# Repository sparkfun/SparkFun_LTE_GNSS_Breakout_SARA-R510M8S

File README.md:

# SparkFun LTE GNSS Breakout - SARA-R510M8S

The u-blox SARA-R510M8S module is a secure cloud LTE Cat M1, LTE Cat NB2 solution based on u-blox's UBX-R5 cellular chipset.
The SARA-R510M8S has an integrated u-blox M8 GNSS receiver chip and a separate GNSS antenna interface.

The SARA-R5's UART interface can be configured into one of five variants, providing connectivity over one or two UARTs. A separate USB port
provides access to the SARA's trace log for diagnostic purposes. This breakout provides access to all three interfaces (UART1, UART2 and SARA Diag)
via three separate USB-C connections. All eight 3.3V serial signals are available on a 0.1"-pitch breakout header.

## Repository Contents

- **/Documentation** - Datasheets etc.
- **/Hardware** - Eagle PCB, SCH and LBR design files. Full schematic in PDF format.
- **[LICENSE.md](./LICENSE.md)** - License details

## Documentation

- **[SparkFun u-blox SARA-R5 Arduino Library](https://github.com/sparkfun/SparkFun_u-blox_SARA-R5_Arduino_Library)** - Arduino library for the SARA-R5 module.
- **[Hookup Guide](https://learn.sparkfun.com/tutorials/lte-gnss-breakout---sara-r5-hookup-guide)** - Hookup Guide for the LTE GNSS Breakout - SARA-R5.

## UART 1 & 2

The board comes pre-configured to support interface variants 0 and 1 (single UART, 8-wire connectivity). If you want to use variants 2-4 (dual UART),
you will need to:
- Open the split pads adjacent to the **DTR**, **DCD**, **RI** and **DSR** breakout pins
- Close the solder split pads labelled **TXD2**, **RXD2**, **RTS2** and **CTS2**
- Open the **OUT** split pad labelled **DSR O RTS2 I** and close the adjacent **IN** solder split pad

The serial signals on the breakout pins are all 3.3V. Level-shifting circuits connect them to the SARA's 1.8V UART pins.

## Power Options

The board can draw 5V power from any or all of the USB-C connectors. Optionally, you can provide power via the **V EXT** breakout pin: 3.7V Min; 6.0V Max.

If you want to use **V EXT** as an output, you can bypass the DVEXT protection diode by closing the **V EXT Diode** solder split pad.

The board's 3.3V current draw can be monitored via the **MEAS** header pins. Open the split pad linking these pins if required.

## Additional Breakout Pins

- **NI** - Network Indicator will be _low_ when the SARA is on and the network is available.
- **TP** - GNSS Timing Pulse (PPS) pin will pulse low/high when configured by the **+UTIME=1,1** command. Please see the [AT Commands Manual](./Documents/SARA-R5_ATCommands_(UBX-19047455).pdf) for more details.
- **SARA On** - pull low for 5 seconds then release to turn the SARA off. Pull low briefly again to turn the SARA back on. You can tell if the SARA is powered by monitoring the **VCCIO** 1.8V pin.
- **INT** - by default this pin is connected to the SARA's bi-directional **EXT INT** pin. It can optionally be connected to **GPIO3** by reconfiguring the **SARA INT** split pad.
- **~RESET** - pull low and release to reset the SARA.
- **SARA I<sup>2</sup>C** - provides access to the SARA's I<sup>2</sup>C SDA and SCL pins.
- **3V3EN** - pull this pin low to disable the 3.3V supply completely. _Note: you may want to turn the SARA off using the **SARA On** pin first, so it disconnects from the network correctly._

**NI**, **TP**, **SARA On**, **INT**, **~RESET**, **SDA** and **SCL** are all 3.3V. Level-shifting circuits connect them to the SARA's 1.8V I/O pins.

_**Important Note**: **VCCIO** is 1.8V. You may need to connect it to an analog input to sense the voltage correctly._

_**Important Note**: **3V3EN** is pulled-up to VIN (5V) via a 100K resistor. We recommend using a switch or open-collector / open-drain output to pull **3V3EN** low._

## Switches

- **Reset** - pressing this switch will reset the SARA.
- **SARA On** - pressing and holding this switch for five seconds will turn the SARA off. Press briefly to turn the SARA back on again.

## GNSS Antenna Power

The board provides 3.3V power for an active GNSS antenna. By default the antenna power is enabled whenever the SARA is on. You can reconfigure the **ANT GNSS PWR**
split pad to optionally control the antenna power via the SARA's GPIO2 pin.

The GPIO2 pin can be controlled using the **+UGPIOC=23,0,1** command.
Please see the [AT Commands Manual](./Documents/SARA-R5_ATCommands_(UBX-19047455).pdf) for more details.

## Product Versions

- [GPS-18031](https://www.sparkfun.com/products/18031) - Initial Release

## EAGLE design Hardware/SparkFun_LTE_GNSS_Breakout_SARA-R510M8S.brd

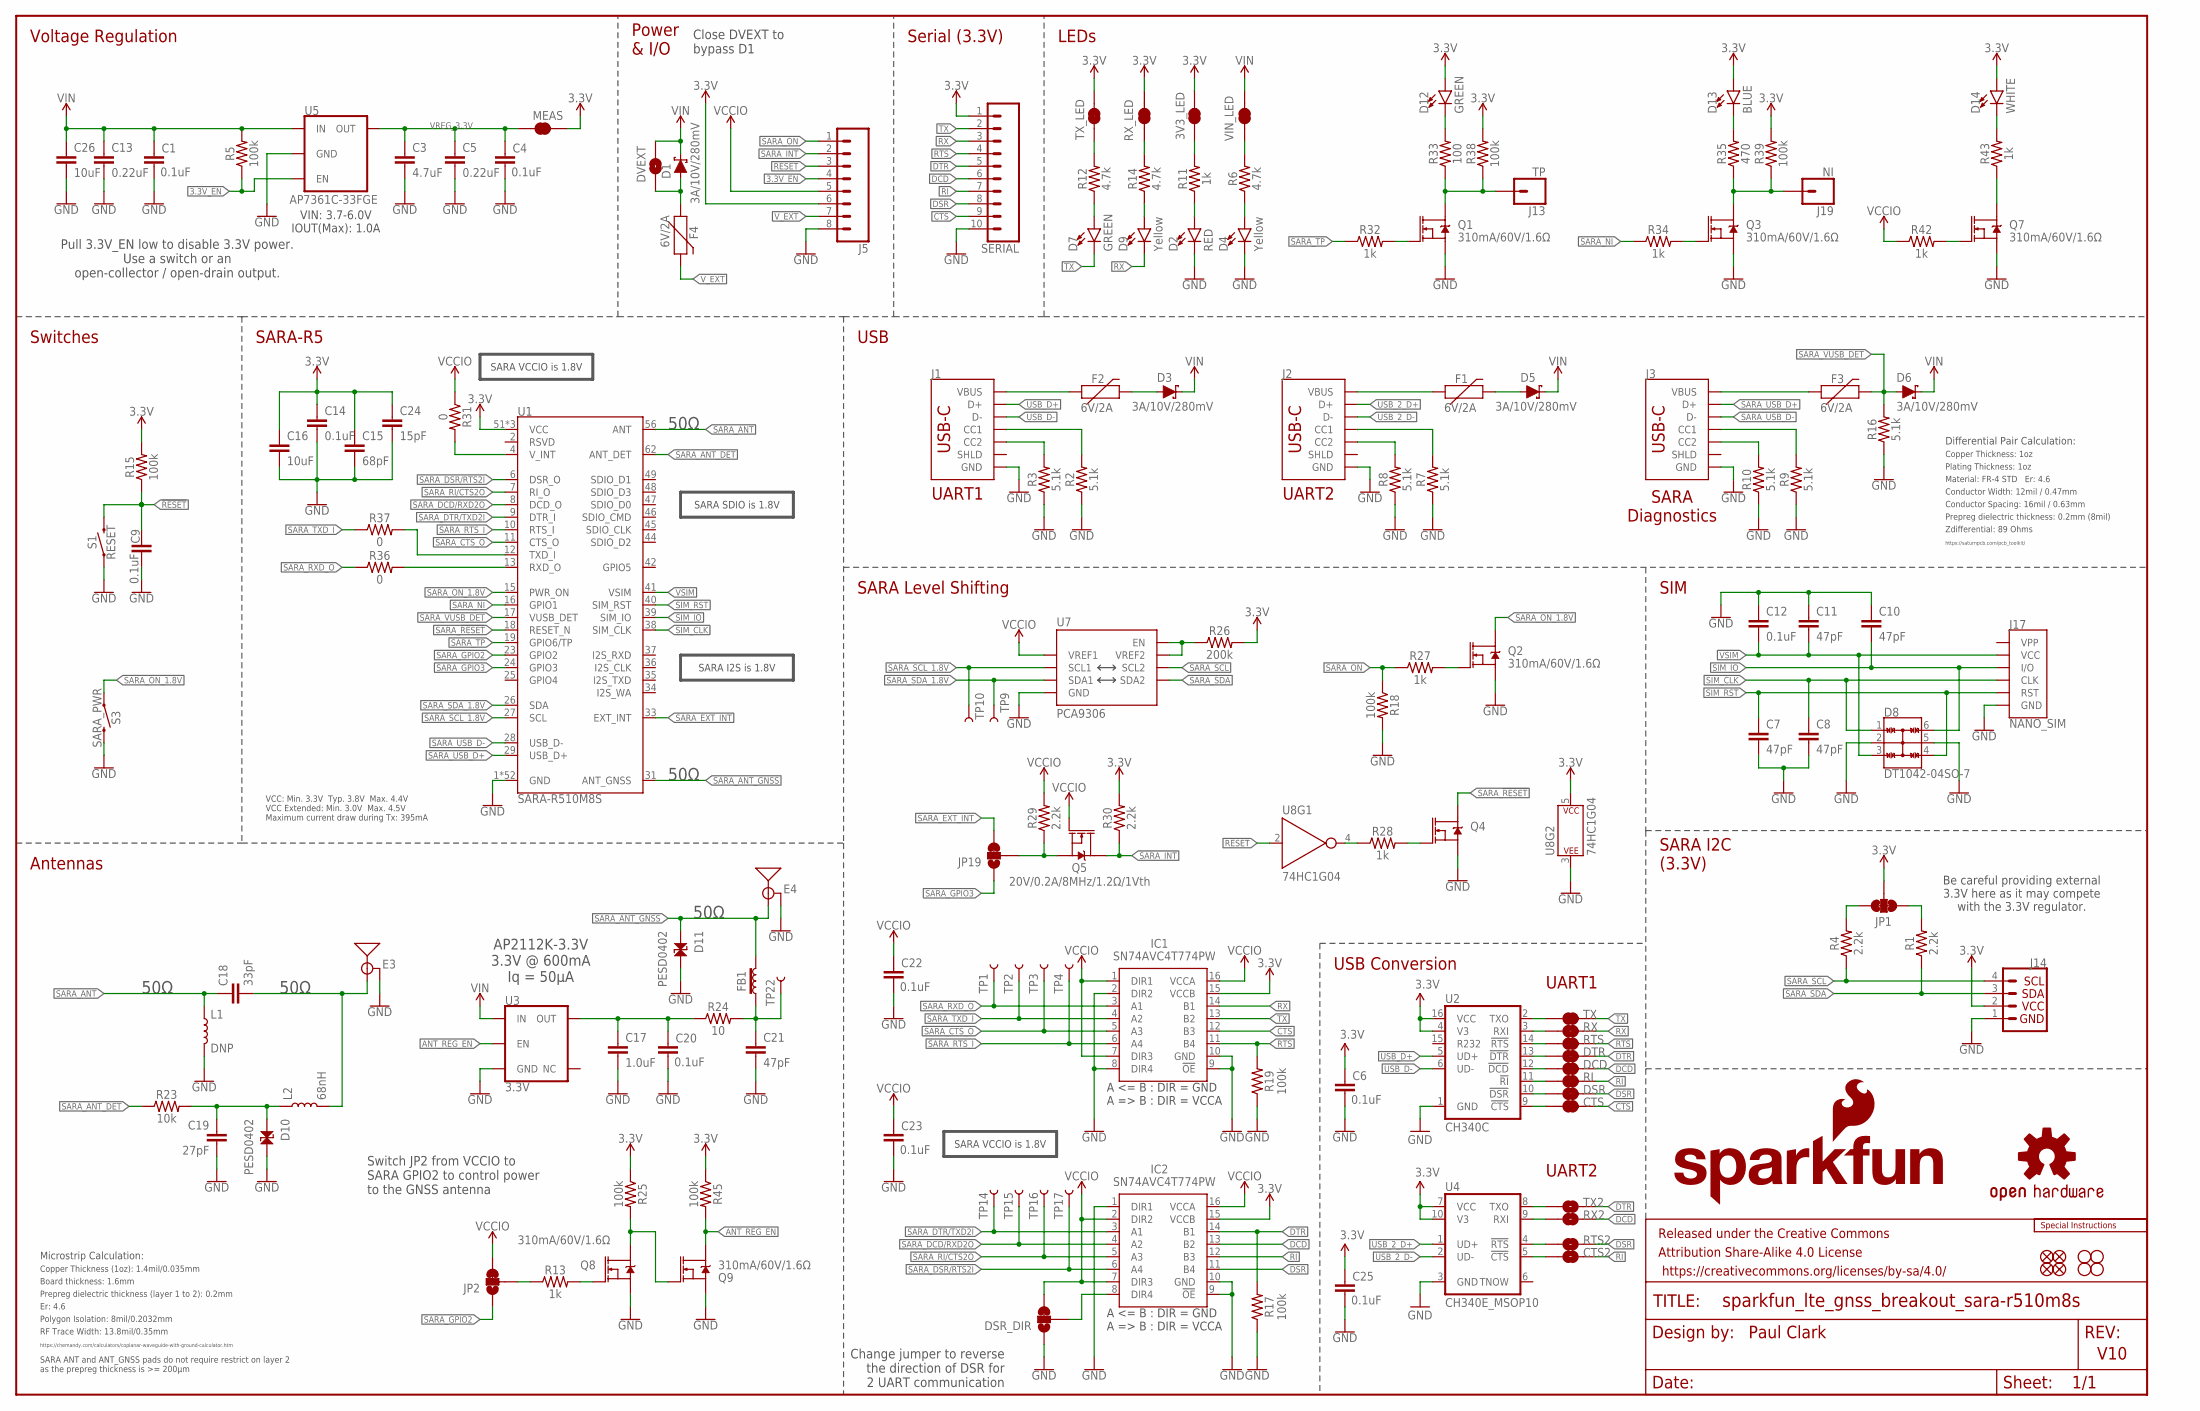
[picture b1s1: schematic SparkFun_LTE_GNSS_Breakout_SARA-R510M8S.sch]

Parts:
3V3_LED: JUMPER-SMT_2_NC_TRACE_SILK; SMT-JUMPER_2_NC_TRACE_SILK
C1, C4, C6, C9, C12, C14, C20, C22, C23, C25: 0.1uF; 0603
C3: 4.7uF; 0603
C5, C13: 0.22uF; 0603
C7, C8, C10, C11, C21: 47pF; 0603
C15: 68pF; 0603
C16: 10uF; 0603
C17: 1.0uF; 0603
C18: 33pF; 0402-TIGHT
C19: 27pF; 0402
C24: 15pF; 0603
C26: 10uF; 0805
CTS: JUMPER-SMT_2_NC_TRACE_SILK; SMT-JUMPER_2_NC_TRACE_SILK
CTS2: JUMPER-SMT_2_NO_SILK; SMT-JUMPER_2_NO_SILK
D1, D3, D5, D6: 3A/10V/280mV; SOD-323
D2: RED; LED-0603
D4, D9: Yellow; LED-0603
D7, D12: GREEN; LED-0603
D8: DT1042-04SO-7; SOT23-6L
D10, D11: PESD0402; 0402
D13: BLUE; LED-0603
D14: WHITE; LED-0603
DCD: JUMPER-SMT_2_NC_TRACE_SILK; SMT-JUMPER_2_NC_TRACE_SILK
DSR: JUMPER-SMT_2_NC_TRACE_SILK; SMT-JUMPER_2_NC_TRACE_SILK
DSR_DIR: JUMPER-SMT_3_1-NC_TRACE_SILK; SMT-JUMPER_3_1-NC_TRACE_SILK
DTR: JUMPER-SMT_2_NC_TRACE_SILK; SMT-JUMPER_2_NC_TRACE_SILK
DVEXT: JUMPER-SMT_2_NO_SILK; SMT-JUMPER_2_NO_SILK
E3, E4: ANTENNA-SMA-GROUNDEDEDGE_SMA_SMD; SMA-EDGE-SMD
F1, F2, F3, F4: 6V/2A; 1210
FB1: 30Ω/1.8A; 0603
FD1, FD2, FD3, FD4: FIDUCIALUFIDUCIAL; FIDUCIAL-MICRO
FRAME1: FRAME-LEDGER; CREATIVE_COMMONS
H1, H2, H3, H4: STAND-OFF
IC1, IC2: SN74AVC4T774PW; SOP65P640X120-16N
J1, J2, J3: USB_C_4-LAYER_PADS; USB-C-16P_4LAYER-PADS
J5: CONN_08NO_SILK_DNP; 1X08_NO_SILK
J13: TP; 1X01_NO_SILK
J14: I2C_STANDARD_NO_SILK; 1X04_NO_SILK
J17: NANO_SIM; NANO_SIM_WURTH_693043020611
J19: NI; 1X01_NO_SILK
JP1: JUMPER-SMT_3_2-NC_TRACE_SILK; SMT-JUMPER_3_2-NC_TRACE_SILK
JP2, JP19: JUMPER-SMT_3_1-NC_TRACE_SILK; SMT-JUMPER_3_1-NC_TRACE_SILK
L1: DNP; 0402_COILCRAFT
L2: 68nH; 0402_COILCRAFT
LOGO1: SFE_LOGO_NAME_FLAME.1_INCH; SFE_LOGO_NAME_FLAME_.1
LOGO3: OSHW-LOGOMINI; OSHW-LOGO-MINI
LOGO5: SPECIAL_INSTRUCTIONS-ORDERING; ORDERING_INSTRUCTIONS
MEAS: JUMPER-COMBO_2_NC_TRACE; COMBO-JUMPER_2_NC_TRACE
Q1, Q2, Q3, Q4, Q7, Q8, Q9: 310mA/60V/1.6Ω; SOT323
Q5: 20V/0.2A/8MHz/1.2Ω/1Vth; SOT-416FL
R1, R4, R29, R30: 2.2k; 0603
R2, R3, R7, R8, R9, R10, R16: 5.1k; 0603
R5, R15, R17, R18, R19, R25, R38, R39, R45: 100k; 0603
R6, R12, R14: 4.7k; 0603
R11, R13, R27, R28, R32, R34, R42, R43: 1k; 0603
R23: 10k; 0603
R24: 10; 0603
R26: 200k; 0603
R31, R36, R37: 0; 0603
R33: 100; 0603
R35: 470; 0603
RI: JUMPER-SMT_2_NC_TRACE_SILK; SMT-JUMPER_2_NC_TRACE_SILK
RTS: JUMPER-SMT_2_NC_TRACE_SILK; SMT-JUMPER_2_NC_TRACE_SILK
RTS2: JUMPER-SMT_2_NO_SILK; SMT-JUMPER_2_NO_SILK
RX: JUMPER-SMT_2_NC_TRACE_SILK; SMT-JUMPER_2_NC_TRACE_SILK
RX2: JUMPER-SMT_2_NO_SILK; SMT-JUMPER_2_NO_SILK
RX_LED: JUMPER-SMT_2_NC_TRACE_SILK; SMT-JUMPER_2_NC_TRACE_SILK
S1: RESET; TACTILE_SWITCH_SMD_5.2MM
S3: SARA_PWR; TACTILE_SWITCH_SMD_5.2MM
SERIAL: CONN_10NO_SILK_PTH_FEMALE; 1X10_NO_SILK
TP1, TP2, TP3, TP4, TP9, TP10, TP14, TP15, TP16, TP17, TP22: TEST-POINT3; PAD.03X.03
TX: JUMPER-SMT_2_NC_TRACE_SILK; SMT-JUMPER_2_NC_TRACE_SILK
TX2: JUMPER-SMT_2_NO_SILK; SMT-JUMPER_2_NO_SILK
TX_LED: JUMPER-SMT_2_NC_TRACE_SILK; SMT-JUMPER_2_NC_TRACE_SILK
U1: SARA-R510M8S; SARA-LGA
U2: CH340C; SO016
U3: 3.3V; SOT23-5
U4: CH340E_MSOP10; MSOP10
U5: AP7361C-33FGE; UDFN-8
U7: PCA9306; VSSOP_8PIN
U8: 74HC1G04; SOT353
VIN_LED: JUMPER-SMT_2_NC_TRACE_SILK; SMT-JUMPER_2_NC_TRACE_SILK

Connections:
3.3V: 3V3_LED.2, C6.1, C14.1, C15.1, C16.1, C24.1, C25.1, D12.A, D13.A, D14.A, IC1.15 (VCCB), IC2.15 (VCCB), J5.6, J14.2, JP1.2, MEAS.2, MEAS.4 (2), R15.2, R25.1, R26.2, R30.2, R38.2, R39.2, R45.1, RX_LED.2, SERIAL.1, TX_LED.2, U1.51 (VCC), U1.52 (VCC), U1.53 (VCC), U2.4 (V3), U2.16 (VCC), U4.7 (VCC), U4.10 (V3), U8.5 (P$V+)
3.3V_EN: J5.4, R5.1, U5.5 (EN)
!RESET!: C9.1, J5.3, R15.1, S1.3 (2), S1.4 (2), U8.2 (A)
ANT_REG_EN: Q9.3 (D), R45.2, U3.3 (EN)
CTS: CTS.2, IC1.12 (B3), SERIAL.9
DCD: DCD.2, IC2.13 (B2), RX2.2, SERIAL.6
DSR: DSR.2, IC2.11 (B4), RTS2.2, SERIAL.8
DTR: DTR.2, IC2.14 (B1), R17.2, SERIAL.5, TX2.2
GND: C1.2, C3.2, C4.2, C5.2, C6.2, C7.2, C8.2, C9.2, C10.1, C11.1, C12.1, C13.2, C14.2, C15.2, C16.2, C17.2, C19.2, C20.2, C21.2, C22.2, C23.2, C24.2, C25.2, C26.2, D2.C, D4.C, D8.2, D8.5, D10.2, D11.2, DSR_DIR.1, E3.GND@0 (GND), E3.GND@1 (GND), E4.GND@0 (GND), E4.GND@1 (GND), IC1.2 (DIR2), IC1.8 (DIR4), IC1.9 (!OE), IC1.10 (GND), IC2.1 (DIR1), IC2.9 (!OE), IC2.10 (GND), J1.GND, J1.GND2 (GND), J2.GND, J2.GND2 (GND), J3.GND, J3.GND2 (GND), J5.8, J14.1, J17.C5 (GND), L1.P$2 (2), Q1.2 (S), Q2.2 (S), Q3.2 (S), Q4.2 (S), Q7.2 (S), Q8.2 (S), Q9.2 (S), R2.1, R3.1, R7.1, R8.1, R9.1, R10.1, R16.1, R17.1, R18.2, R19.1, S1.1, S1.2 (1), S3.3 (2), S3.4 (2), SERIAL.10, U1.1 (GND), U1.3 (GND), U1.5 (GND), U1.14 (GND), U1.20 (GND), U1.21 (GND), U1.22 (GND), U1.30 (GND), U1.32 (GND), U1.43 (GND), U1.50 (GND), U1.54 (GND), U1.55 (GND), U1.57 (GND), U1.58 (GND), U1.59 (GND), U1.60 (GND), U1.61 (GND), U1.63 (GND), U1.64 (GND), U1.65 (GND), U1.66 (GND), U1.67 (GND), U1.68 (GND), U1.69 (GND), U1.70 (GND), U1.71 (GND), U1.72 (GND), U1.73 (GND), U1.74 (GND), U1.75 (GND), U1.76 (GND), U1.77 (GND), U1.78 (GND), U1.79 (GND), U1.80 (GND), U1.81 (GND), U1.82 (GND), U1.83 (GND), U1.84 (GND), U1.85 (GND), U1.86 (GND), U1.87 (GND), U1.88 (GND), U1.89 (GND), U1.90 (GND), U1.91 (GND), U1.92 (GND), U1.93 (GND), U1.94 (GND), U1.95 (GND), U1.96 (GND), U2.1 (GND), U3.2 (GND), U4.3 (GND), U5.4 (GND), U5.EP (GND), U7.P1 (GND), U8.3 (P$V-)
unnamed: R6.2, VIN_LED.1
unnamed: JP1.3, R4.2
unnamed: JP1.1, R1.2
unnamed: D3.A, F2.2
unnamed: J2.A5 (CC1), R7.2
unnamed: 3V3_LED.1, R11.2
unnamed: D2.A, R11.1
unnamed: D4.A, R6.1
unnamed: J2.B5 (CC2), R8.2
unnamed: J1.A5 (CC1), R2.2
unnamed: J1.B5 (CC2), R3.2
unnamed: D5.A, F1.2
unnamed: F1.1, J2.VBUS1 (VBUS), J2.VBUS2 (VBUS)
unnamed: J3.A5 (CC1), R9.2
unnamed: C18.2, E3.SIG (SIGNAL), L2.P$2 (2)
unnamed: C19.1, D10.1, L2.P$1 (1), R23.2
unnamed: J3.B5 (CC2), R10.2
unnamed: F3.1, J3.VBUS1 (VBUS), J3.VBUS2 (VBUS)
unnamed: F2.1, J1.VBUS1 (VBUS), J1.VBUS2 (VBUS)
unnamed: TX.1, U2.2 (TXO)
unnamed: RX.1, U2.3 (RXI)
unnamed: R26.1, U7.P7 (VREF2), U7.P8 (EN)
unnamed: DSR_DIR.2, IC2.8 (DIR4)
unnamed: C17.1, C20.1, R24.1, U3.5 (OUT)
unnamed: C21.1, FB1.1, R24.2, TP22.P$1
unnamed: Q2.1 (G), R27.2
unnamed: Q4.1 (G), R28.2
unnamed: R28.1, U8.4 (Y)
unnamed: RTS.1, U2.14 (!RTS)
unnamed: DTR.1, U2.13 (!DTR)
unnamed: R31.2, U1.4 (V_INT)
unnamed: Q1.1 (G), R32.2
unnamed: J13.1, Q1.3 (D), R33.1, R38.1
unnamed: D12.C, R33.2
unnamed: Q3.1 (G), R34.2
unnamed: J19.1, Q3.3 (D), R35.1, R39.1
unnamed: D13.C, R35.2
unnamed: R36.2, U1.13 (RXD_O)
unnamed: R37.2, U1.12 (TXD_I)
unnamed: Q8.1 (G), R13.2
unnamed: DCD.1, U2.12 (!DCD)
unnamed: Q8.3 (D), Q9.1 (G), R25.2
unnamed: JP19.2, Q5.2 (S), R29.1
unnamed: RI.1, U2.11 (!RI)
unnamed: DSR.1, U2.10 (!DSR)
unnamed: CTS.1, U2.9 (!CTS)
unnamed: Q7.1 (G), R42.2
unnamed: TX2.1, U4.8 (TXO)
unnamed: D14.C, R43.2
unnamed: RX2.1, U4.9 (RXI)
unnamed: RTS2.1, U4.4 (!RTS)
unnamed: CTS2.1, U4.5 (!CTS)
unnamed: R12.2, TX_LED.1
unnamed: D7.A, R12.1
unnamed: R14.2, RX_LED.1
unnamed: D9.A, R14.1
unnamed: D1.A, DVEXT.1, F4.1
unnamed: JP2.2, R13.1
RI: CTS2.2, IC2.12 (B3), RI.2, SERIAL.7
RTS: IC1.11 (B4), R19.2, RTS.2, SERIAL.4
RX: D9.C, IC1.14 (B1), RX.2, SERIAL.3
SARA_!ON!: Q7.3 (D), R43.1
SARA_!RESET!: Q4.3 (D), U1.18 (RESET_N)
SARA_ANT: C18.1, L1.P$1 (1), U1.56 (ANT)
SARA_ANT_DET: R23.1, U1.62 (ANT_DET)
SARA_ANT_GNSS: D11.1, E4.SIG (SIGNAL), FB1.2, U1.31 (ANT_GNSS)
SARA_CTS_O: IC1.5 (A3), TP3.P$1, U1.11 (CTS_O)
SARA_DCD/RXD2O: IC2.4 (A2), TP15.P$1, U1.8 (DCD_O)
SARA_DSR/RTS2I: IC2.6 (A4), TP17.P$1, U1.6 (DSR_O)
SARA_DTR/TXD2I: IC2.3 (A1), TP14.P$1, U1.9 (DTR_I)
SARA_EXT_INT: JP19.3, U1.33 (EXT_INT)
SARA_GPIO2: JP2.1, U1.23 (GPIO2)
SARA_GPIO3: JP19.1, U1.24 (GPIO3)
SARA_INT: J5.2, Q5.3 (D), R30.1
SARA_NI: R34.1, U1.16 (GPIO1)
SARA_ON: J5.1, R18.1, R27.1
SARA_ON_1.8V: Q2.3 (D), S3.1, S3.2 (1), U1.15 (PWR_ON)
SARA_RI/CTS2O: IC2.5 (A3), TP16.P$1, U1.7 (RI_O)
SARA_RTS_I: IC1.6 (A4), TP4.P$1, U1.10 (RTS_I)
SARA_RXD_O: IC1.3 (A1), R36.1, TP1.P$1
SARA_SCL: J14.4, R4.1, U7.P6 (SCL2)
SARA_SCL_1.8V: TP10.P$1, U1.27 (SCL), U7.P3 (SCL1)
SARA_SDA: J14.3, R1.1, U7.P5 (SDA2)
SARA_SDA_1.8V: TP9.P$1, U1.26 (SDA), U7.P4 (SDA1)
SARA_TP: R32.1, U1.19 (GPIO6/TP)
SARA_TXD_I: IC1.4 (A2), R37.1, TP2.P$1
SARA_USB_D+: J3.A6 (D+), J3.B6 (D+), U1.29 (USB_D+)
SARA_USB_D-: J3.A7 (D-), J3.B7 (D-), U1.28 (USB_D-)
SARA_VUSB_DET: D6.A, F3.2, R16.2, U1.17 (VUSB_DET)
SIM_CLK: C8.1, D8.1, J17.C3 (CLK), U1.38 (SIM_CLK)
SIM_IO: C10.2, D8.6, J17.C7 (I/O), U1.39 (SIM_IO)
SIM_RST: C7.1, D8.4, J17.C2 (RST), U1.40 (SIM_RST)
TX: D7.C, IC1.13 (B2), SERIAL.2, TX.2
USB_2_D+: J2.A6 (D+), J2.B6 (D+), U4.1 (UD+)
USB_2_D-: J2.A7 (D-), J2.B7 (D-), U4.2 (UD-)
USB_D+: J1.A6 (D+), J1.B6 (D+), U2.5 (UD+)
USB_D-: J1.A7 (D-), J1.B7 (D-), U2.6 (UD-)
VCCIO: C22.1, C23.1, DSR_DIR.3, IC1.1 (DIR1), IC1.7 (DIR3), IC1.16 (VCCA), IC2.2 (DIR2), IC2.7 (DIR3), IC2.16 (VCCA), J5.5, JP2.3, Q5.1 (G), R29.2, R31.1, R42.1, U7.P2 (VREF1)
VIN: C1.1, C13.1, C26.1, D1.C, D3.C, D5.C, D6.C, DVEXT.2, R5.2, U3.1 (IN), U5.8 (IN), VIN_LED.2
VREG_3.3V: C3.1, C4.1, C5.1, MEAS.1, MEAS.3 (1), U5.1 (OUT)
VSIM: C11.2, C12.2, D8.3, J17.C1 (VCC), U1.41 (VSIM)
V_EXT: F4.2, J5.7

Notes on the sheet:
USB
Voltage Regulation
Paul Clark
V10
VIN: 3.7-6.0V IOUT(Max): 1.0A
LEDs
Switches
SARA-R5
SIM
SARA SDIO is 1.8V
50Ω
SARA I2S is 1.8V
Power & I/O
SARA I2C (3.3V)
Be careful providing external 3.3V here as it may compete with the 3.3V regulator.
SARA VCCIO is 1.8V
Plating Thickness: 1oz
Material: FR-4 STD Er: 4.6
Copper Thickness: 1oz
Conductor Spacing: 16mil / 0.63mm
Conductor Width: 12mil / 0.47mm
Prepreg dielectric thickness: 0.2mm (8mil)
https://saturnpcb.com/pcb_toolkit/
Differential Pair Calculation:
Zdifferential: 89 Ohms
Antennas
VCC: Min. 3.3V Typ. 3.8V Max. 4.4V VCC Extended: Min. 3.0V Max. 4.5V Maximum current draw during Tx: 395mA
Board thickness: 1.6mm
Er: 4.6
Copper Thickness (1oz): 1.4mil/0.035mm
RF Trace Width: 13.8mil/0.35mm
Polygon Isolation: 8mil/0.2032mm
Prepreg dielectric thickness (layer 1 to 2): 0.2mm
https://chemandy.com/calculators/coplanar-waveguide-with-ground-calculator.htm
Microstrip Calculation:
SARA ANT and ANT_GNSS pads do not require restrict on layer 2 as the prepreg thickness is >= 200µm
AP2112K-3.3V 3.3V @ 600mA Iq = 50µA
SARA Level Shifting
Change jumper to reverse the direction of DSR for 2 UART communication
USB Conversion

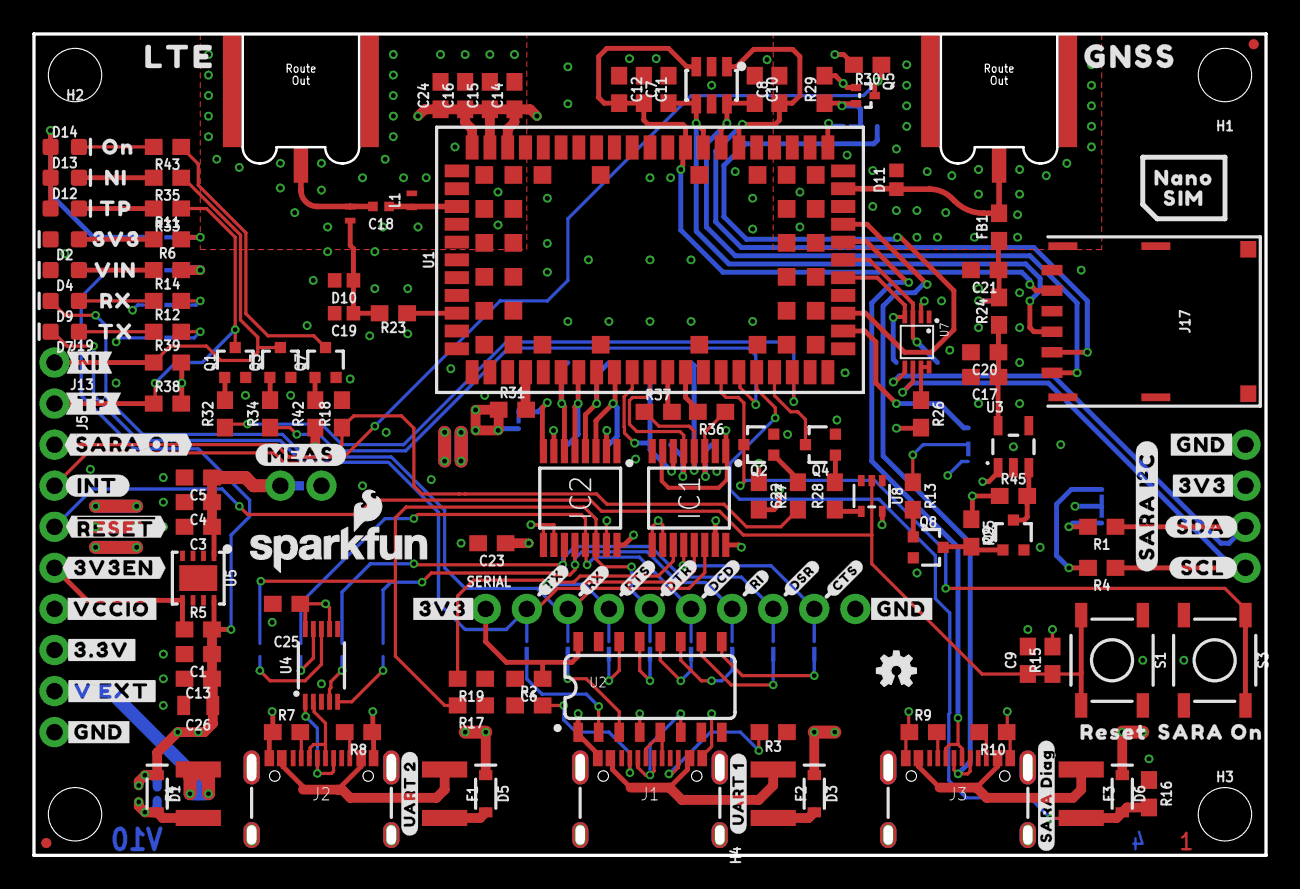
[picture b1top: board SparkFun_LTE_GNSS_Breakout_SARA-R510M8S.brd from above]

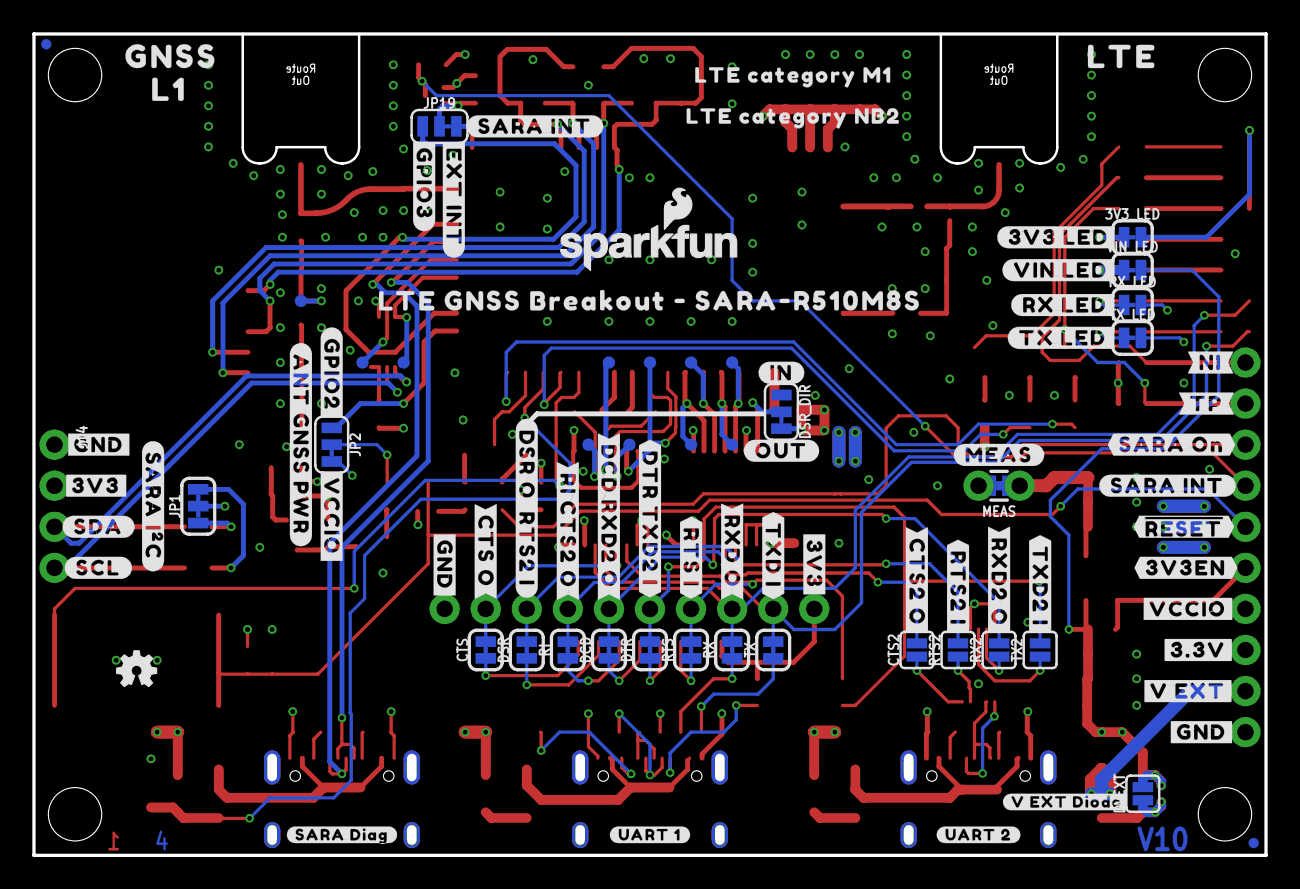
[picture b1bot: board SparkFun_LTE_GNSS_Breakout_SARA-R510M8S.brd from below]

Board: 4 copper layers, 76.2 x 50.8 mm, 256 parts (90 on the bottom side), 111 nets.

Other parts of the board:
LOGO2: OSHW-LOGOMINI; OSHW-LOGO-MINI
LOGO4: SFE_LOGO_NAME_FLAME.1_INCH; SFE_LOGO_NAME_FLAME_.1
U$1, U$2, U$3, U$11: #3V3#1
U$4: #TX_LED#0
U$5, U$23: #SARA_I�C#0
U$6, U$7: #V_EXT#0
U$8, U$9: #3V3EN#0
U$10, U$13: ##RESET##0
U$12, U$22: #GND#0
U$14: #INT#0
U$15, U$71: #SARA_INT#0
U$16, U$17: #SARA_ON#0
U$18: RX0
U$19, U$87: #MEAS#2
U$20: #RX_LED#0
U$21: TX0
U$24: #TX#0
U$25: #RX#0
U$26, U$27: #SCL#3
U$28: #RTS#0
U$29: #DTR#0
U$30, U$37: #SDA#2
U$31: #DCD#0
U$32: #RI#0
U$33: #DSR#0
U$34: #CTS#0
U$35: #RXD_O#0
U$36: 3V37
U$38: #TXD_I#0
U$39: #CTS_O#0
U$40: #RTS_I#0
U$41: #DTR_TXD2_I#0
U$42: L10
U$43: #DCD_RXD2_O#0
U$44: #RXD2_O#0
U$45: RESET6
U$46: VIN8
U$47: #RI_CTS2_O#0
U$48: #CTS2_O#0
U$49: #DSR_O__RTS2_I#0
U$50: #RTS2_I#0
U$51: #V_EXT_DIODE#0
U$52: #OUT#0
U$53: #IN#0
U$54: #VIN_LED#0
U$55, U$56, U$81, U$82: #GND#4
U$57, U$58: #TP#0
U$59, U$60: #NI#0
U$61: #3V3_LED#0
U$62, U$63: #UART_2#0
U$64, U$65: #UART_1#0
U$66, U$67: #SARA_DIAG#0
U$68, U$80, U$83: #VCCIO#0
U$69: #GPIO2#0
U$70: #ANT_GNSS_PWR#0
U$72: #TXD2_I#0
U$73: LTE_CATEGORY_M10
U$74: LTE_CATEGORY_NB20
U$75: LTE_GNSS_BREAKOUT_#_SARA#R510M8S0
U$76, U$79: #3#3V#0
U$88, U$89: LTE0
U$90: NI0
U$91: TP0
U$99, U$100: GNSS0
U$101: ON0
U$113: SARA_ON0
U$118: #EXT_INT#0
U$119: #GPIO3#0
U$130: NANO0
U$131: SIM0

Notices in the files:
parts and their libraries:
SparkFun-Aesthetics: Licensing: Creative Commons ShareAlike 4.0 International - https://creativecommons.org/licenses/by-sa/4.0
SparkFun-Aesthetics: Released under the Creative Commons Attribution Share-Alike 4.0 License
SparkFun-Aesthetics: https://creativecommons.org/licenses/by-sa/4.0
